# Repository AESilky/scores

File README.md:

# Score Board

Two team score board w/remote for use in the yard when playing different games
like ladder-ball, cornhole, horseshoes, basketball, etc.

Options for two display types:

1. 2 Digits each for Team-A, Team-B, and a third for Period, Time, etc., and 4 indicators for each team.
2. 2 Linear rows of 24 dots each (for Team-A and Team-B), and 4 indicators for each team.

The Digits type is a typical score board that you would use for baseball,
basketball, football, etc. The Linear display is appropriate for games that
go from 0 to some number of points (maximum of 24), like cornhole, ladderball,
horseshoes, etc.

It uses either a remote or switch banks to control the score. It can use the
remote alone, or with a switch bank, or with two switch banks (without the remote).
The switch banks have either 4 or 6 switches. When using two switch banks, there
is a bank for each team that allow increasing/decreasing the score, resetting to
a lower score (typically 11) and to zero.

The board has a Zigby receiver for non line of sight, communication (though not
yet supported).

The board uses multiplexed 7 segment LED displays to provide a two team/player
two digit score, plus a two digit number that can count periods, innings,
quarters, etc., or can count down/up time. There are four LEDs under the score
for each side that can be used to indicate timeouts left, substitutions made,
etc.

The linear display is also multiplexed LEDs, using the segment drives.

The board also has a OLED display panel (SPI) that can also display the score (intended
for the back side to assist a scorekeeper), as well as for use for setup.

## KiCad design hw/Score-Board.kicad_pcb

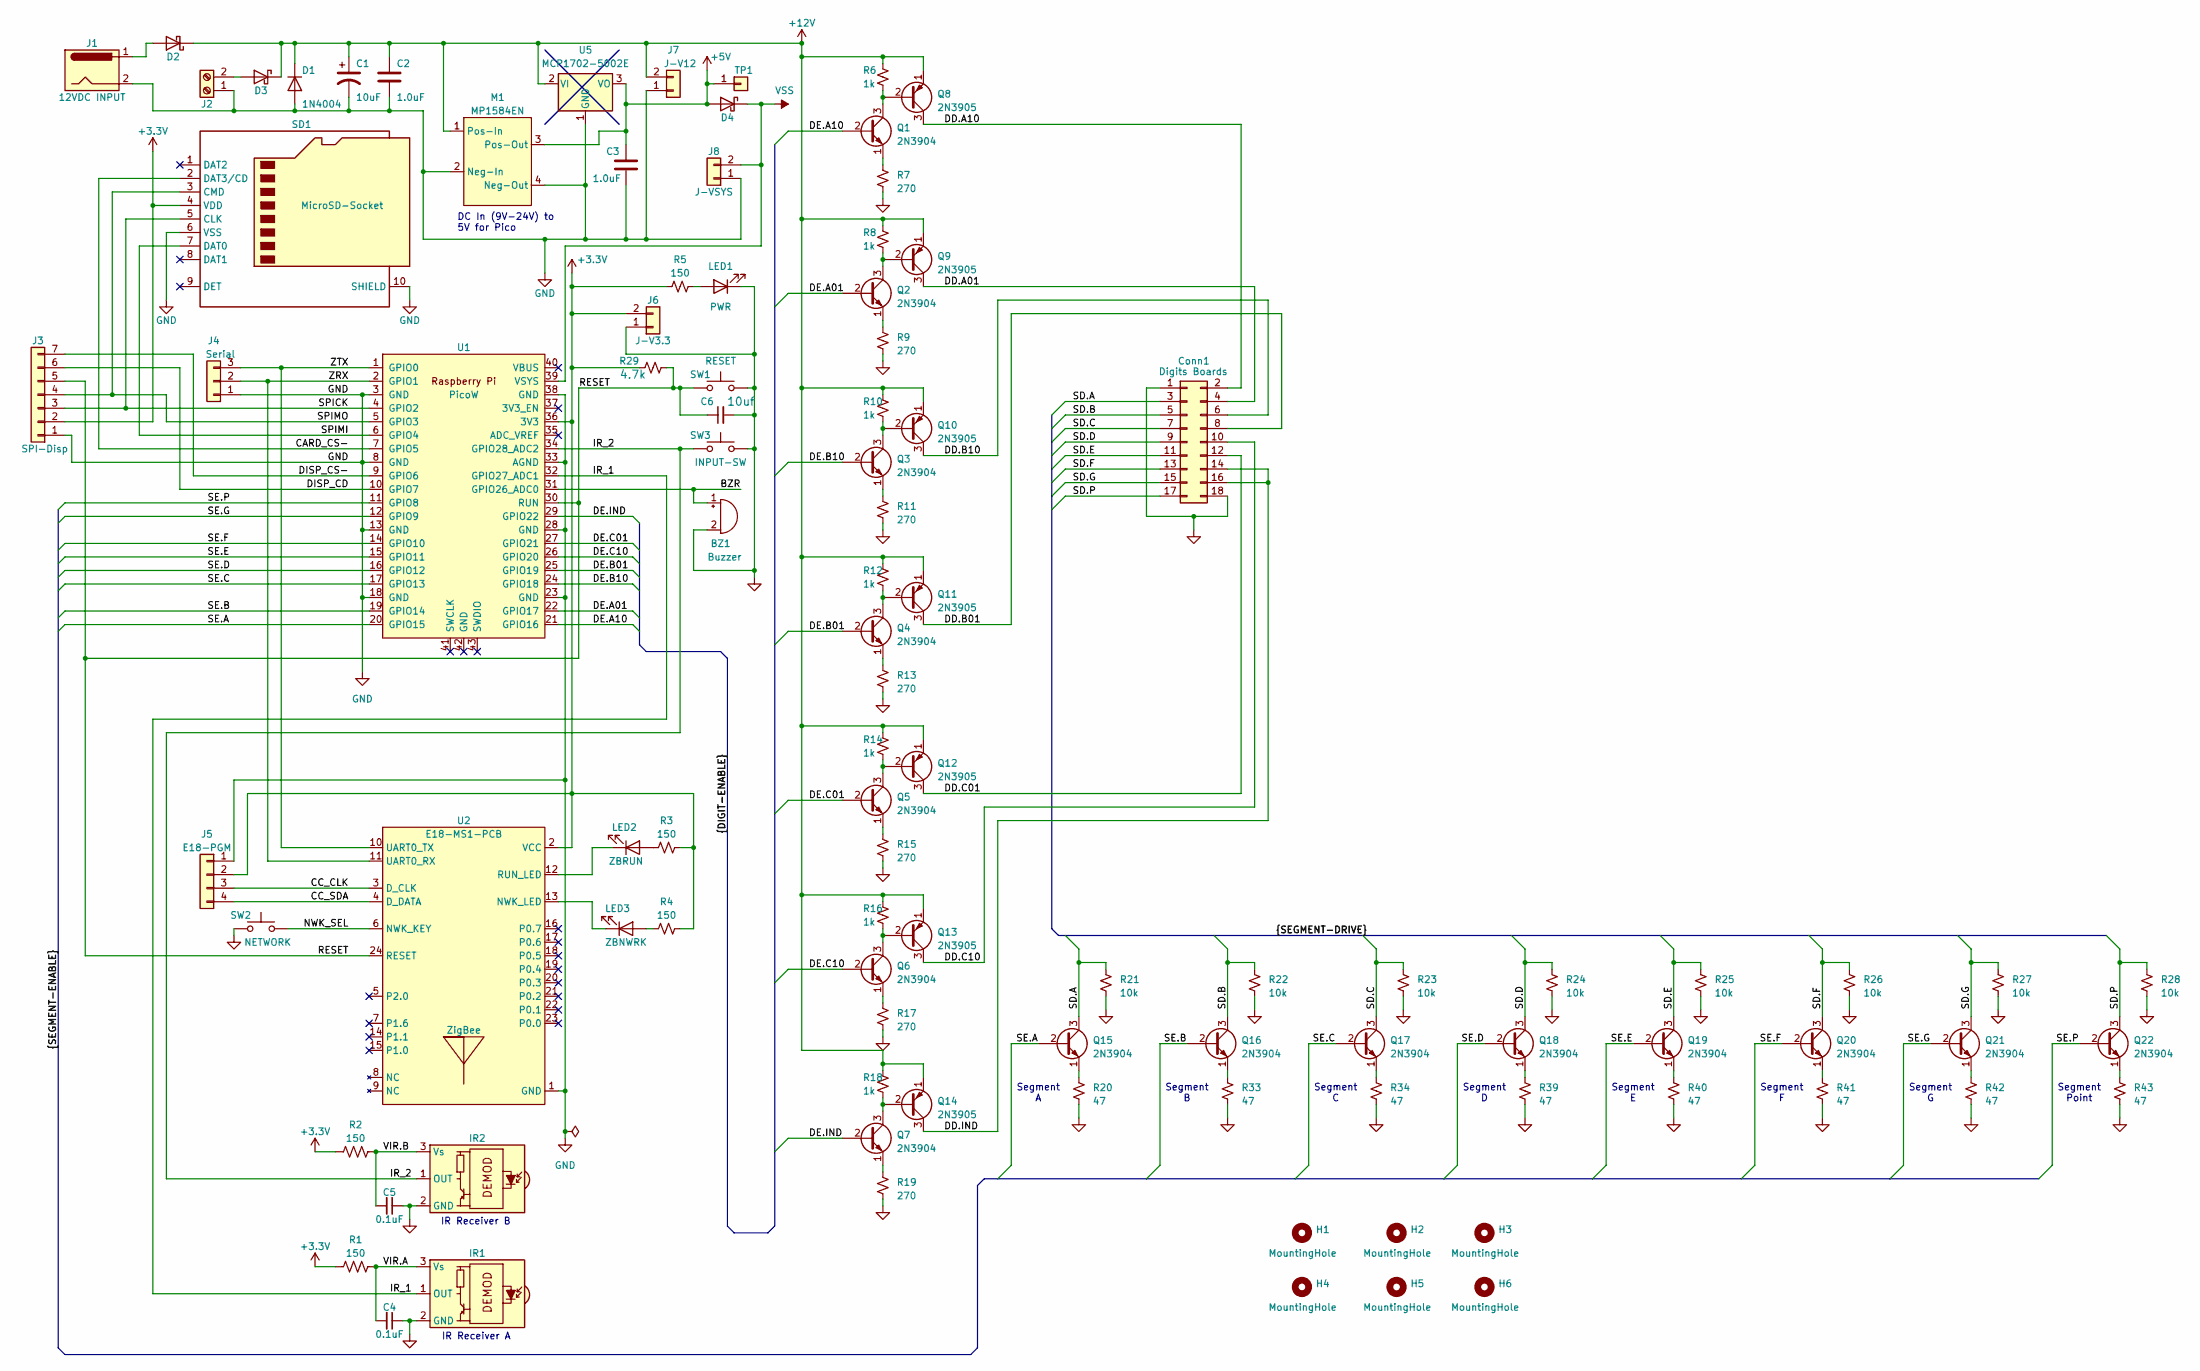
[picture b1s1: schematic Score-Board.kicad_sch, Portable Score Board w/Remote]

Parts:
BZ1: Buzzer; Buzzer_12x9.5RM7.6
C1: 10uF; CP_Radial_D8.0mm_P3.50mm
C2, C3: 1.0uF; CP_Radial_D5.0mm_P2.00mm
C4, C5: 0.1uF; C_Disc_D5.0mm_W2.5mm_P2.50mm
C6: 10uf
Conn1: Conn_02x09_Odd_Even; PinHeader_2x09_P2.54mm_Vertical
D1: 1N4004; D_DO-41_SOD81_P10.16mm_Horizontal
D2, D4: D_Schottky_PP; D_DO-35_SOD27_P10.16mm_Horizontal
D3: D_Schottky; D_DO-35_SOD27_P10.16mm_Horizontal
H1, H2, H3, H4, H5, H6: MountingHole; MountingHole_3.2mm_M3
IR1, IR2: TSOP382xx; Vishay_MINICAST-3Pin
J1: Barrel_Jack; CUI_PJ-037B
J2: Screw_Terminal_01x02; TerminalBlock_Philmore_TB132_1x02_P5.00mm_Horizontal
J3: SPI-Disp; PinSocket_1x07_P2.54mm_Vertical
J4: Conn_01x03; PinHeader_1x03_P2.54mm_Vertical
J5: Conn_01x04; PinHeader_1x04_P2.54mm_Vertical
J6: J-V3.3; PinHeader_1x02_P2.54mm_Vertical
J7: J-V12; PinHeader_1x02_P2.54mm_Vertical
J8: J-VSYS; PinHeader_1x02_P2.54mm_Vertical
LED1: PWR; LED_D5.0mm
LED2: ZBRUN; LED_D5.0mm
LED3: ZBNWRK; LED_D5.0mm
M1: MP1584EN
Q1, Q2, Q3, Q4, Q5, Q6, Q7, Q15, Q16, Q17, Q18, Q19, Q20, Q21, Q22: 2N3904; TO-92_Inline
Q8, Q9, Q10, Q11, Q12, Q13, Q14: 2N3905; TO-92_Inline
R1, R2, R3, R4, R5: 150; R_Axial_DIN0207_L6.3mm_D2.5mm_P10.16mm_Horizontal
R6, R8, R10, R12, R14, R16, R18: 1k; R_Axial_DIN0207_L6.3mm_D2.5mm_P10.16mm_Horizontal
R7, R9, R11, R13, R15, R17, R19: 270; R_Axial_DIN0207_L6.3mm_D2.5mm_P10.16mm_Horizontal
R20, R33, R34, R39, R40, R41, R42, R43: 47; R_Axial_DIN0207_L6.3mm_D2.5mm_P10.16mm_Horizontal
R21, R22, R23, R24, R25, R26, R27, R28: 10k; R_Axial_DIN0207_L6.3mm_D2.5mm_P10.16mm_Horizontal
R29: 4.7k; R_Axial_DIN0207_L6.3mm_D2.5mm_P10.16mm_Horizontal
SD1: MicroSD-Socket; SDCard-GCT_MEM2075-00-140-01-A
SW1: RESET; SW_TL1100F160Q
SW2: NETWORK; SW_TL1100F160Q
SW3: INPUT-SW; SW_TL1100F160Q
TP1: Conn_01x01; PinHeader_1x01_P2.54mm_Vertical
U1: PicoW; RPi_PicoW_SMD_TH
U2: E18-MS1-PCB; E18-MS1-PCB-AES
U5: MCP1702-5002E; TO-92_Inline

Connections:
+3.3V: J3.2, J5.2, J6.2, R1.1 (I), R2.1 (I), R3.2, R4.2, R5.1, R29.1, SD1.4 (VDD), U1.36 (3V3), U2.2 (VCC)
+5V: C3.1, D4.2 (A), M1.3 (Pos-Out), TP1.1, U5.3 (VO)
+12V: C1.1, C2.1, D1.1 (K), D2.1 (K), D3.1 (K), J7.2, M1.1 (Pos-In), Q8.1 (E), Q9.1 (E), Q10.1 (E), Q11.1 (E), Q12.1 (E), Q13.1 (E), Q14.1 (E), R6.1, R8.1, R10.1, R12.1, R14.1, R16.1, R18.1, U5.2 (VI)
/BZR: BZ1.1 (-), U1.31 (GPIO26_ADC0)
/CARD_CS-: SD1.2 (DAT3/CD), U1.7 (GPIO5)
/CC_CLK: J5.3, U2.3 (D_CLK)
/CC_SDA: J5.4, U2.4 (D_DATA)
/DD.A01: Conn1.4, Q9.3 (C)
/DD.A10: Conn1.2, Q8.3 (C)
/DD.B01: Conn1.8, Q11.3 (C)
/DD.B10: Conn1.6, Q10.3 (C)
/DD.C01: Conn1.12, Q12.3 (C)
/DD.C10: Conn1.10, Q13.3 (C)
/DD.IND: Conn1.14, Conn1.16, Q14.3 (C)
/DE.A01: Q2.2 (B), U1.22 (GPIO17)
/DE.A10: Q1.2 (B), U1.21 (GPIO16)
/DE.B01: Q4.2 (B), U1.25 (GPIO19)
/DE.B10: Q3.2 (B), U1.24 (GPIO18)
/DE.C01: Q5.2 (B), U1.27 (GPIO21)
/DE.C10: Q6.2 (B), U1.26 (GPIO20)
/DE.IND: Q7.2 (B), U1.29 (GPIO22)
/DISP_CD: J3.6, U1.10 (GPIO7)
/DISP_CS-: J3.7, U1.9 (GPIO6)
/IR_1: IR1.1 (OUT), U1.32 (GPIO27_ADC1)
/IR_2: IR2.1 (OUT), SW3.1, U1.34 (GPIO28_ADC2)
/NWK_SEL: SW2.2, U2.6 (NWK_KEY)
/RESET: C6.1, J3.5, R29.2, SW1.1, U1.30 (RUN), U2.24 (RESET)
/SD.A: Conn1.3, Q15.3 (C), R21.1
/SD.B: Conn1.5, Q16.3 (C), R22.1
/SD.C: Conn1.7, Q17.3 (C), R23.1
/SD.D: Conn1.9, Q18.3 (C), R24.1
/SD.E: Conn1.11, Q19.3 (C), R25.1
/SD.F: Conn1.13, Q20.3 (C), R26.1
/SD.G: Conn1.15, Q21.3 (C), R27.1
/SD.P: Conn1.17, Q22.3 (C), R28.1
/SE.A: Q15.2 (B), U1.20 (GPIO15)
/SE.B: Q16.2 (B), U1.19 (GPIO14)
/SE.C: Q17.2 (B), U1.17 (GPIO13)
/SE.D: Q18.2 (B), U1.16 (GPIO12)
/SE.E: Q19.2 (B), U1.15 (GPIO11)
/SE.F: Q20.2 (B), U1.14 (GPIO10)
/SE.G: Q21.2 (B), U1.12 (GPIO9)
/SE.P: Q22.2 (B), U1.11 (GPIO8)
/SPICK: J3.3, SD1.5 (CLK), U1.4 (GPIO2)
/SPIMI: SD1.7 (DAT0), U1.6 (GPIO4)
/SPIMO: J3.4, SD1.3 (CMD), U1.5 (GPIO3)
/VIR.A: C4.2, IR1.3 (Vs), R1.2 (O)
/VIR.B: C5.2, IR2.3 (Vs), R2.2 (O)
/ZRX: J4.2, U1.2 (GPIO1), U2.11 (UART0_RX)
/ZTX: J4.3, U1.1 (GPIO0), U2.10 (UART0_TX)
GND: BZ1.2 (+), C1.2, C2.2, C3.2, C4.1, C5.1, C6.2, Conn1.1, Conn1.18, D1.2 (A), IR1.2 (GND), IR2.2 (GND), J1.2, J2.1, J3.1, J4.1, J5.1, J6.1, J7.1, J8.1, LED1.1 (K), M1.2 (Neg-In), M1.4 (Neg-Out), R7.2, R9.2, R11.2, R13.2, R15.2, R17.2, R19.2, R20.2, R21.2, R22.2, R23.2, R24.2, R25.2, R26.2, R27.2, R28.2, R33.2, R34.2, R39.2, R40.2, R41.2, R42.2, R43.2, SD1.6 (VSS), SD1.10 (SHIELD), SW1.2, SW2.1, SW3.2, U1.3 (GND), U1.8 (GND), U1.13 (GND), U1.18 (GND), U1.23 (GND), U1.28 (GND), U1.33 (AGND), U1.38 (GND), U2.1 (GND), U5.1 (GND)
unnamed: D2.2 (A), J1.1
unnamed: D3.2 (A), J2.2
unnamed: LED1.2 (A), R5.2
unnamed: LED2.2 (A), R3.1
unnamed: LED2.1 (K), U2.12 (RUN_LED)
unnamed: LED3.2 (A), R4.1
unnamed: LED3.1 (K), U2.13 (NWK_LED)
unnamed: Q1.3 (C), Q8.2 (B), R6.2
unnamed: Q1.1 (E), R7.1
unnamed: Q2.3 (C), Q9.2 (B), R8.2
unnamed: Q2.1 (E), R9.1
unnamed: Q3.1 (E), R11.1
unnamed: Q4.1 (E), R13.1
unnamed: Q5.1 (E), R15.1
unnamed: Q6.1 (E), R17.1
unnamed: Q7.1 (E), R19.1
unnamed: Q3.3 (C), Q10.2 (B), R10.2
unnamed: Q4.3 (C), Q11.2 (B), R12.2
unnamed: Q5.3 (C), Q12.2 (B), R14.2
unnamed: Q6.3 (C), Q13.2 (B), R16.2
unnamed: Q7.3 (C), Q14.2 (B), R18.2
unnamed: Q15.1 (E), R20.1
unnamed: Q16.1 (E), R33.1
unnamed: Q17.1 (E), R34.1
unnamed: Q18.1 (E), R39.1
unnamed: Q19.1 (E), R40.1
unnamed: Q20.1 (E), R41.1
unnamed: Q21.1 (E), R42.1
unnamed: Q22.1 (E), R43.1
VSS: D4.1 (K), J8.2, U1.39 (VSYS)

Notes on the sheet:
Segment E
Segment C
Segment B
Segment D
Segment G
Segment A
Segment F
Segment Point
IR Receiver B
DC In (9V-24V) to 5V for Pico
IR Receiver A

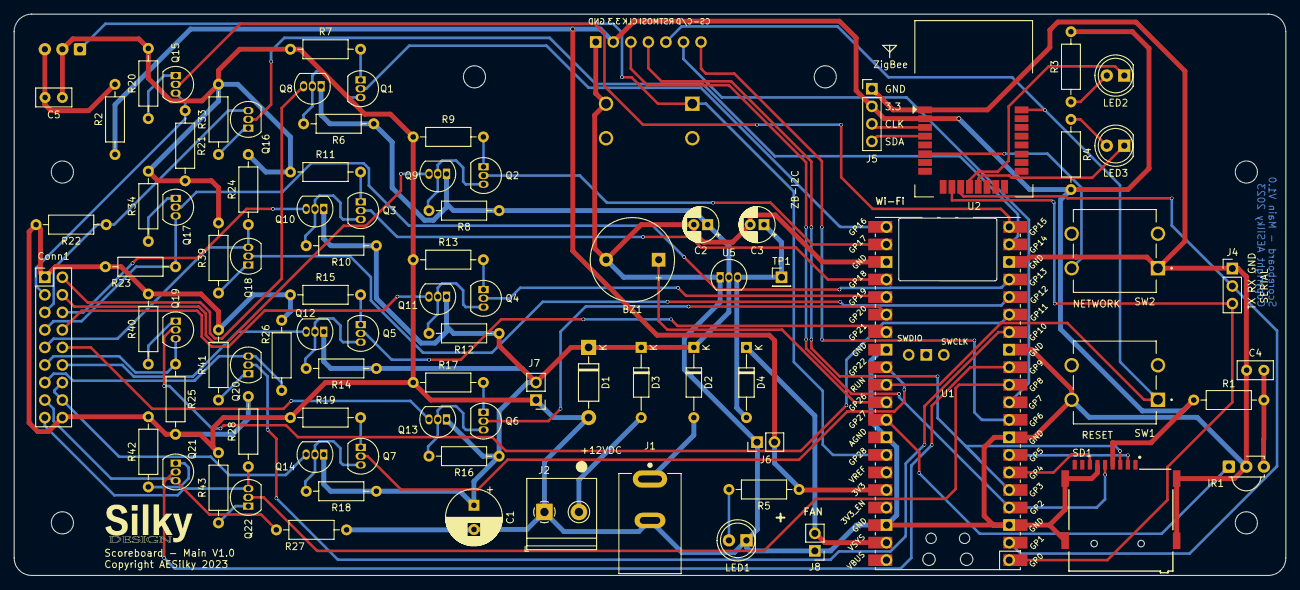
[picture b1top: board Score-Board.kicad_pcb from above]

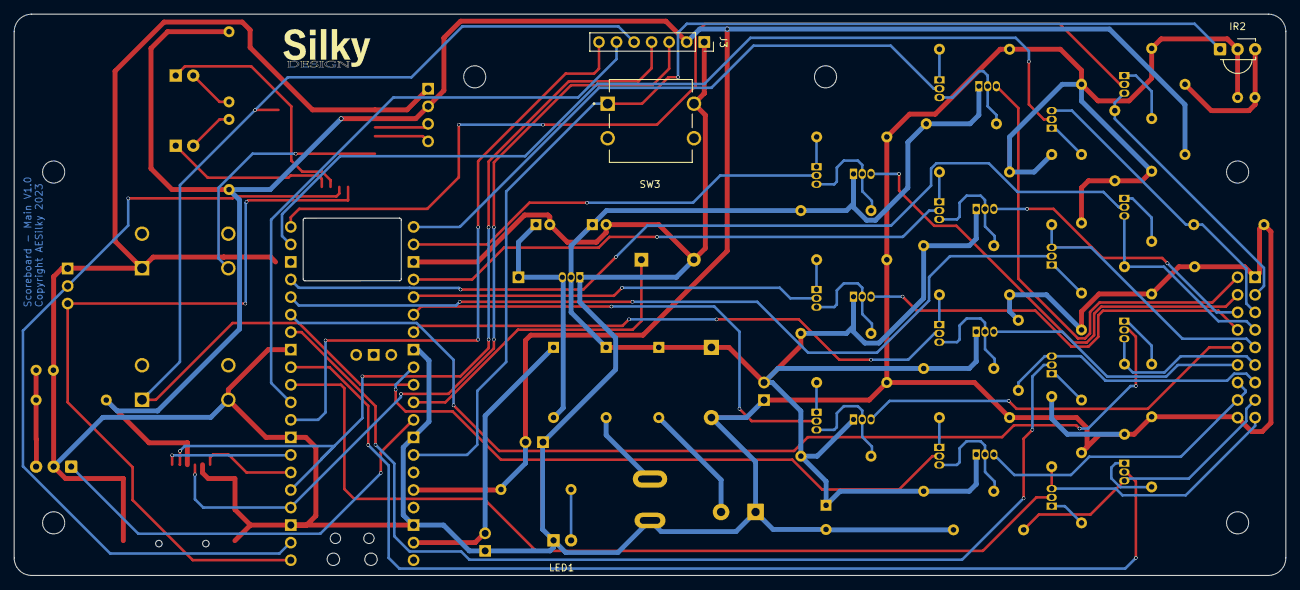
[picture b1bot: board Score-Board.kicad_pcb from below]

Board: 2 copper layers, 184.2 x 81.3 mm, 95 parts (3 on the bottom side), 81 nets.

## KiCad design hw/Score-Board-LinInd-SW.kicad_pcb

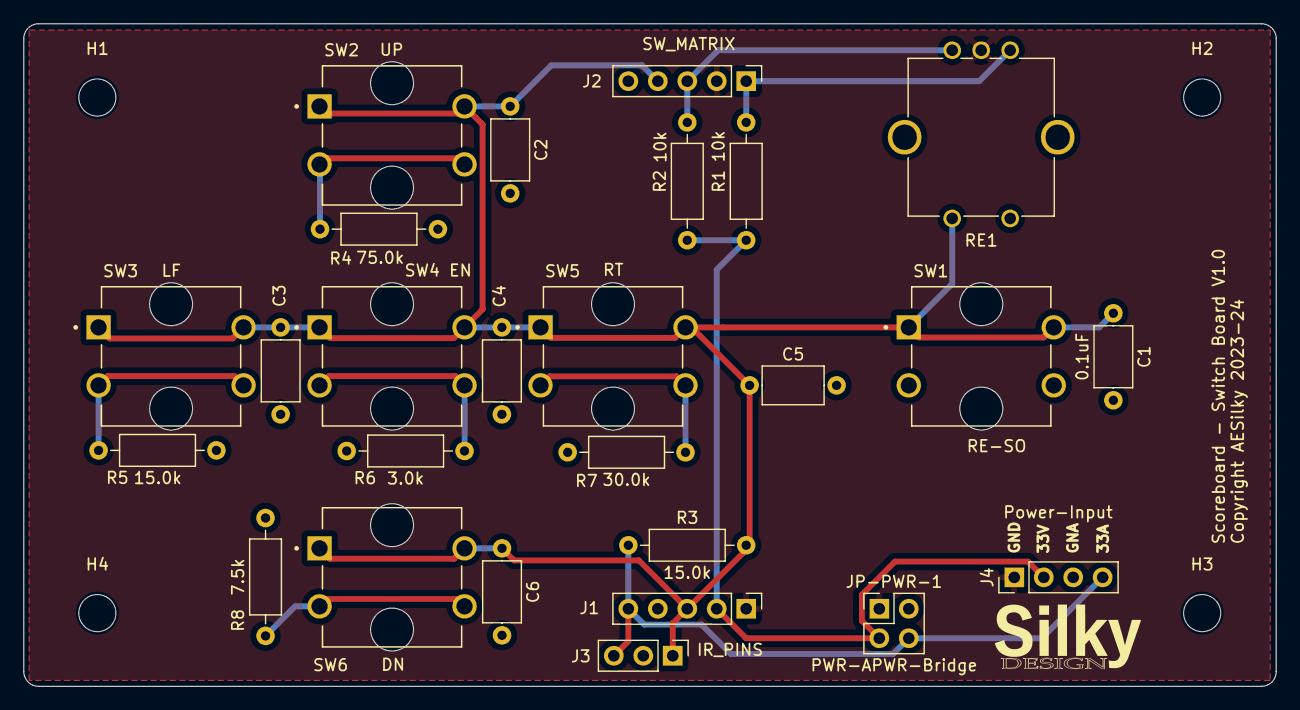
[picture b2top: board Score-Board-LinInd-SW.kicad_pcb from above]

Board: 2 copper layers, 108.0 x 57.1 mm, 31 parts (0 on the bottom side), 12 nets.

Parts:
C1, C2, C3, C4, C5, C6: 0.1uF; C_Axial_L5.1mm_D3.1mm_P7.50mm_Horizontal
G1: LOGO; SILKY-DESIGN-logo-0_50-AES
H1, H2, H3, H4: MountingHole; MountingHole_3.2mm_M3
J1: IR_PINS; PinHeader_1x05_P2.54mm_Vertical
J2: SW_MATRIX; PinHeader_1x05_P2.54mm_Vertical
J3: IR_CONN; PinHeader_1x03_P2.54mm_Vertical
J4: Power-Input; PinHeader_1x04_P2.54mm_Vertical
JP-PWR-1: PWR-APWR-Bridge; PinHeader_2x02_P2.54mm_Vertical
R1, R2: 10k; R_Axial_DIN0207_L6.3mm_D2.5mm_P10.16mm_Horizontal
R3, R5: 15.0k; R_Axial_DIN0207_L6.3mm_D2.5mm_P10.16mm_Horizontal
R4: 75.0k; R_Axial_DIN0207_L6.3mm_D2.5mm_P10.16mm_Horizontal
R6: 3.0k; R_Axial_DIN0207_L6.3mm_D2.5mm_P10.16mm_Horizontal
R7: 30.0k; R_Axial_DIN0207_L6.3mm_D2.5mm_P10.16mm_Horizontal
R8: 7.5k; R_Axial_DIN0207_L6.3mm_D2.5mm_P10.16mm_Horizontal
RE1: RotEnc-SW; RotaryEncoder_Bourns_Vertical_PEC12R-3xxxF-Sxxxx
SW1: RE-SO; AES-SW_PUSH_TH_1P1T_12mm
SW2: UP; AES-SW_PUSH_TH_1P1T_12mm
SW3: LF; AES-SW_PUSH_TH_1P1T_12mm
SW4: EN; AES-SW_PUSH_TH_1P1T_12mm
SW5: RT; AES-SW_PUSH_TH_1P1T_12mm
SW6: DN; AES-SW_PUSH_TH_1P1T_12mm

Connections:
+3.3V: J1.2, J4.2, JP-PWR-1.3, R1.1, R2.1
+3.3VA: J1.5, J3.3, J4.4, JP-PWR-1.4, R3.1
/RE_A: J2.1, R1.2, RE1.A
/RE_B: J2.3, R2.2, RE1.B
/SW_MTRX: C1.1, C2.1, C3.1, C4.1, C5.1, C6.1, J1.3, J2.4, J3.1, R3.2, RE1.S2, SW1.1, SW1.2, SW2.1, SW2.2, SW3.1, SW3.2, SW4.1, SW4.2, SW5.1, SW5.2, SW6.1, SW6.2
GND: J1.1, J2.2, J4.1, JP-PWR-1.1, RE1.C
GNDA: C1.2, C2.2, C3.2, C4.2, C5.2, C6.2, J1.4, J2.5, J3.2, J4.3, JP-PWR-1.2, R4.1, R5.1, R6.1, R7.1, R8.1, RE1.S1, SW1.3, SW1.4
unnamed: R4.2, SW2.3, SW2.4
unnamed: R5.2, SW3.3, SW3.4
unnamed: R6.2, SW4.3, SW4.4
unnamed: R7.2, SW5.3, SW5.4
unnamed: R8.2, SW6.3, SW6.4

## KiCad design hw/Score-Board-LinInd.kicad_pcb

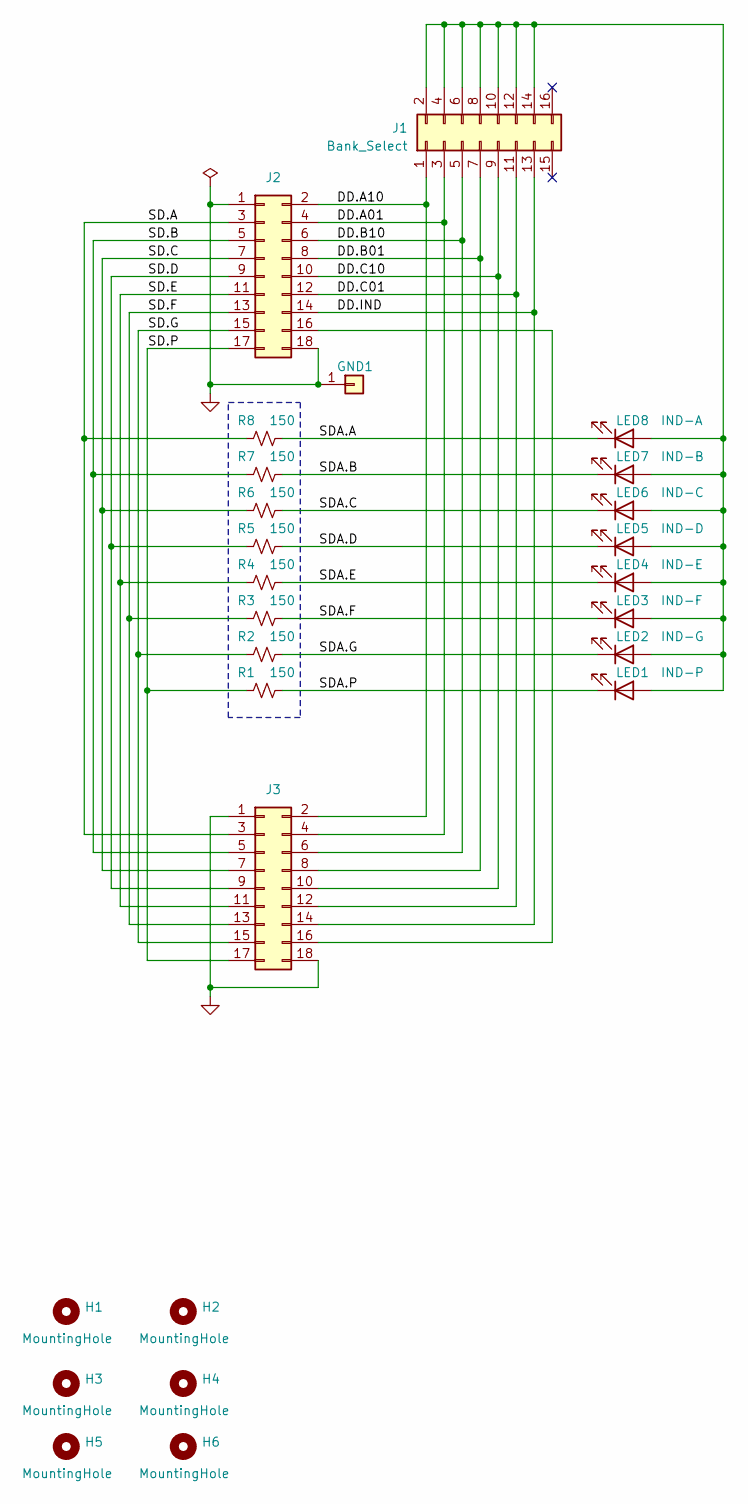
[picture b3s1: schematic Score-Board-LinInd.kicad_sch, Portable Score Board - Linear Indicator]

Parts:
GND1: Conn_01x01; PinHeader_1x01_P2.54mm_Vertical
H1, H2, H3, H4, H5, H6: MountingHole; MountingHole_3.2mm_M3
J1: Bank_Select; PinHeader_2x08_P2.54mm_Vertical
J2, J3: DigSeg-Drive; PinHeader_2x09_P2.54mm_Vertical
LED1: IND-P; LED_D10.0mm
LED2: IND-G; LED_D10.0mm
LED3: IND-F; LED_D10.0mm
LED4: IND-E; LED_D10.0mm
LED5: IND-D; LED_D10.0mm
LED6: IND-C; LED_D10.0mm
LED7: IND-B; LED_D10.0mm
LED8: IND-A; LED_D10.0mm
R1, R2, R3, R4, R5, R6, R7, R8: 150; R_Axial_DIN0207_L6.3mm_D2.5mm_P10.16mm_Horizontal

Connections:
/DD.A01: J1.3, J2.4, J3.4
/DD.A10: J1.1, J2.2, J3.2
/DD.B01: J1.7, J2.8, J3.8
/DD.B10: J1.5, J2.6, J3.6
/DD.C01: J1.11, J2.12, J3.12
/DD.C10: J1.9, J2.10, J3.10
/DD.IND: J1.13, J2.14, J3.14
/SD.A: J2.3, J3.3, R8.1
/SD.B: J2.5, J3.5, R7.1
/SD.C: J2.7, J3.7, R6.1
/SD.D: J2.9, J3.9, R5.1
/SD.E: J2.11, J3.11, R4.1
/SD.F: J2.13, J3.13, R3.1
/SD.G: J2.15, J3.15, R2.1
/SD.P: J2.17, J3.17, R1.1
/SDA.A: LED8.1 (K), R8.2
/SDA.B: LED7.1 (K), R7.2
/SDA.C: LED6.1 (K), R6.2
/SDA.D: LED5.1 (K), R5.2
/SDA.E: LED4.1 (K), R4.2
/SDA.F: LED3.1 (K), R3.2
/SDA.G: LED2.1 (K), R2.2
/SDA.P: LED1.1 (K), R1.2
GND: GND1.1, J2.1, J2.18, J3.1, J3.18
unnamed: J1.2, J1.4, J1.6, J1.8, J1.10, J1.12, J1.14, LED1.2 (A), LED2.2 (A), LED3.2 (A), LED4.2 (A), LED5.2 (A), LED6.2 (A), LED7.2 (A), LED8.2 (A)
unnamed: J2.16, J3.16

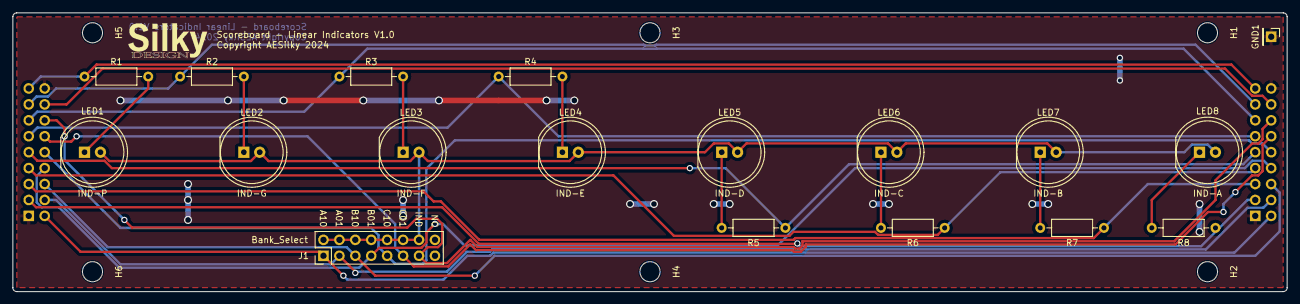
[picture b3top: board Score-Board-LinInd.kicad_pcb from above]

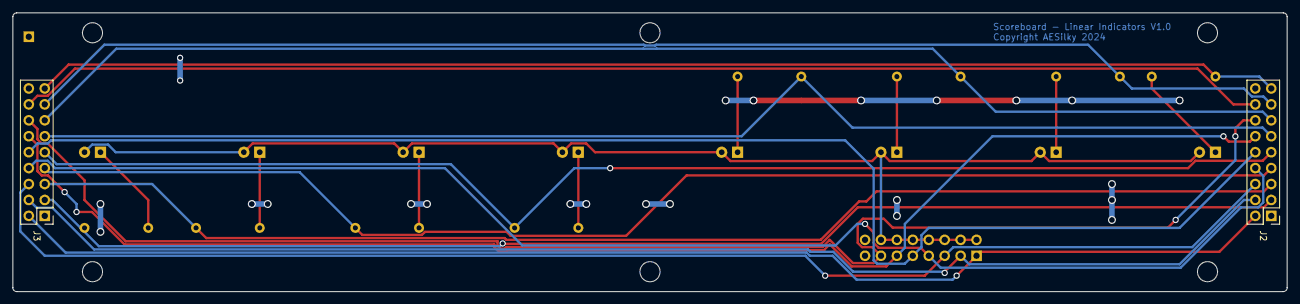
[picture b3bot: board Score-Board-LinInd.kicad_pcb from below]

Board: 2 copper layers, 203.2 x 44.5 mm, 27 parts (2 on the bottom side), 26 nets.

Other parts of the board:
G1: LOGO; SILKY-DESIGN-logo-0_50-AES

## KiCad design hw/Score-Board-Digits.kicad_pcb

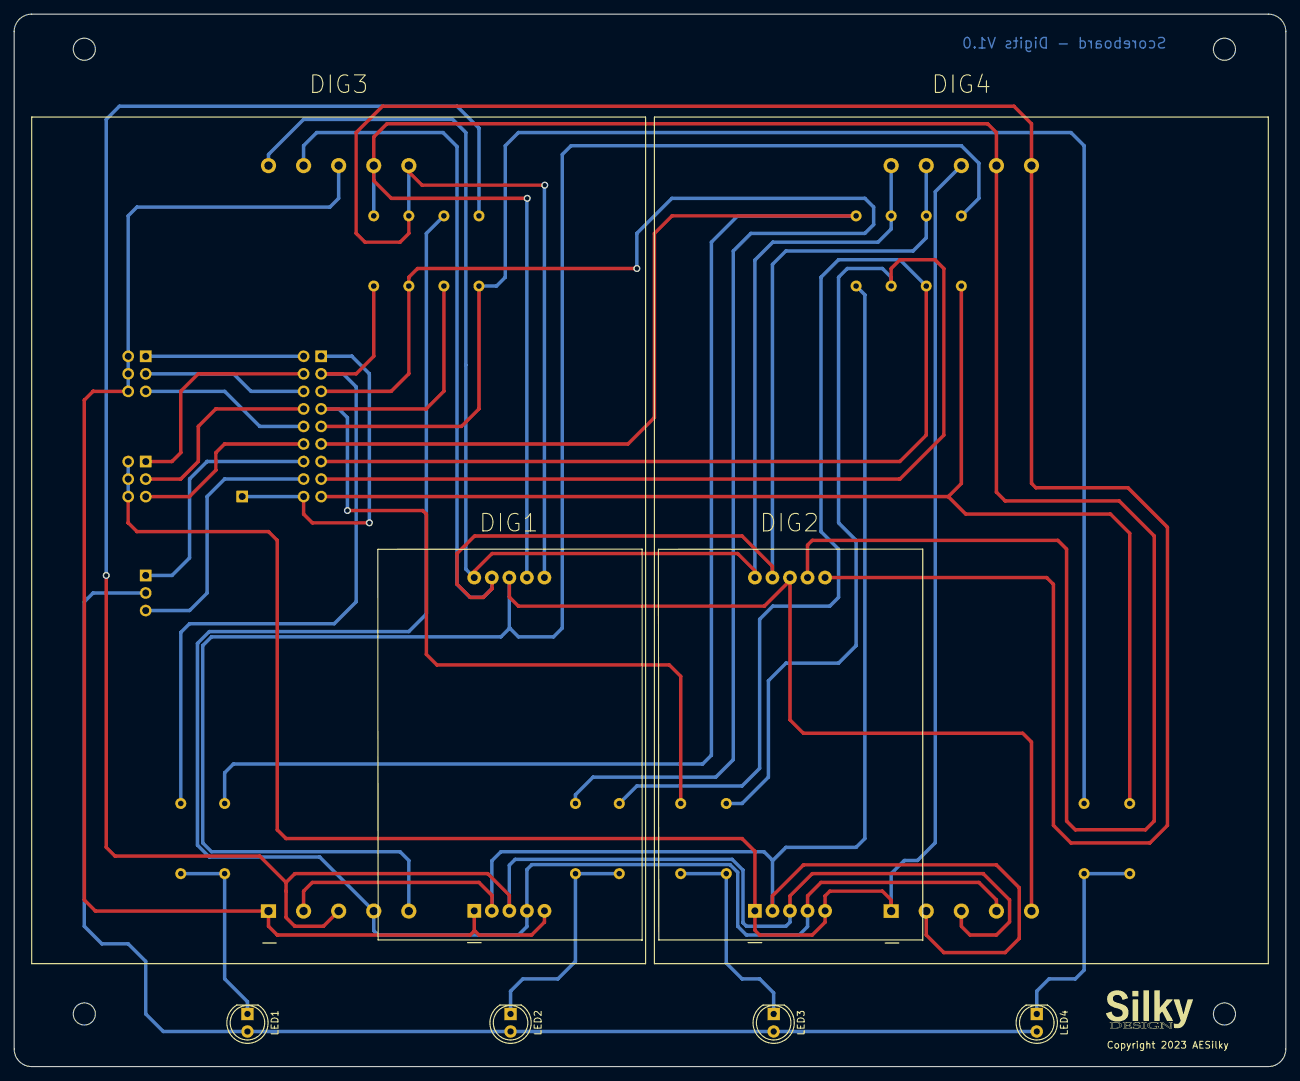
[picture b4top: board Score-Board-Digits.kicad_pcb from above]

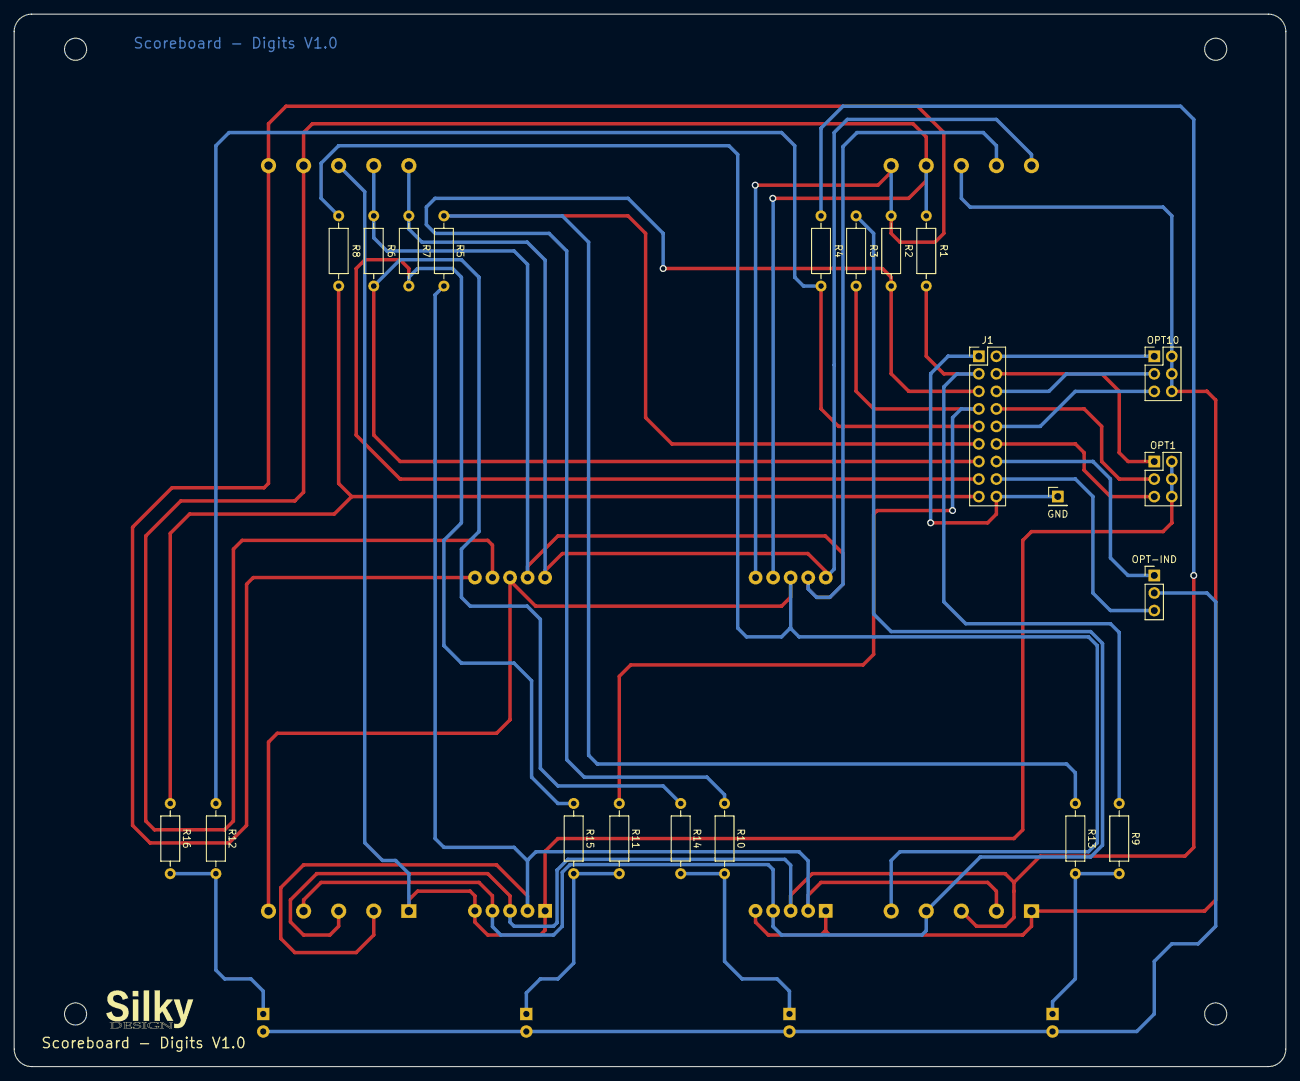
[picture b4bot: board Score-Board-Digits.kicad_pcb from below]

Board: 2 copper layers, 184.1 x 152.4 mm, 33 parts (21 on the bottom side), 32 nets.

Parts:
DIG1, DIG2: WJLEDS18012TUR11; DISP-CL18011BS-AES
DIG3, DIG4: WJLEDS40012TUR11; DISP-40101BCR-AES
GND: Conn_01x01; PinHeader_1x01_P2.54mm_Vertical
H1, H2, H3, H4: MountingHole; MountingHole_3.2mm_M3
J1: Conn_02x09_Odd_Even; PinHeader_2x09_P2.54mm_Vertical
LED1: IND-A1; LED_D5.0mm
LED2: IND-A2; LED_D5.0mm
LED3: IND-A3; LED_D5.0mm
LED4: IND-A4; LED_D5.0mm
OPT1, OPT10: Conn_02x03_Odd_Even; PinHeader_2x03_P2.54mm_Vertical
OPT-IND: Opt_1-2; PinHeader_1x03_P2.54mm_Vertical
R1, R2, R3, R4, R5, R6, R7: 77; R_Axial_DIN0207_L6.3mm_D2.5mm_P10.16mm_Horizontal
R8, R9, R10, R11, R12, R13, R14, R15, R16: 100; R_Axial_DIN0207_L6.3mm_D2.5mm_P10.16mm_Horizontal

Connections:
/SD.A: J1.3, R1.1, R9.1
/SD.B: J1.5, R2.1, R10.1
/SD.C: J1.7, R3.1, R11.1
/SD.D: J1.9, R4.1, R12.1
/SD.E: J1.11, R5.1, R13.1
/SD.F: J1.13, R6.1, R14.1
/SD.G: J1.15, R7.1, R15.1
/SD.P: J1.17, R8.1, R16.1
/SDA.A: DIG1.7 (A), DIG2.7 (A), DIG3.7 (A), DIG4.7 (A), R1.2
/SDA.B: DIG1.6 (B), DIG2.6 (B), DIG3.6 (B), DIG4.6 (B), R2.2
/SDA.C: DIG1.4 (C), DIG2.4 (C), DIG3.4 (C), DIG4.4 (C), R3.2
/SDA.D: DIG1.3 (D), DIG2.3 (D), DIG3.3 (D), DIG4.3 (D), R4.2
/SDA.E: DIG1.2 (E), DIG2.2 (E), DIG3.2 (E), DIG4.2 (E), R5.2
/SDA.F: DIG1.9 (F), DIG2.9 (F), DIG3.9 (F), DIG4.9 (F), R6.2
/SDA.G: DIG1.10 (G), DIG2.10 (G), DIG3.10 (G), DIG4.10 (G), R7.2
/SDA.P: DIG1.8 (DP), DIG2.8 (DP), DIG3.5 (DP), DIG4.5 (DP), R8.2
GND: GND.1, J1.1, J1.18
unnamed: J1.2, OPT10.1
unnamed: J1.4, OPT1.1
unnamed: J1.6, OPT10.3
unnamed: J1.8, OPT1.3
unnamed: J1.10, OPT10.5
unnamed: J1.12, OPT1.5
unnamed: J1.14, OPT-IND.1 (Pin_A)
unnamed: J1.16, OPT-IND.3 (Pin_B)
unnamed: LED1.2 (A), LED2.2 (A), LED3.2 (A), LED4.2 (A), OPT-IND.2 (Pin_Common)
unnamed: LED1.1 (K), R9.2, R13.2
unnamed: LED2.1 (K), R10.2, R14.2
unnamed: LED3.1 (K), R11.2, R15.2
unnamed: LED4.1 (K), R12.2, R16.2
unnamed: DIG2.1 (CA), DIG2.5 (CA), DIG4.1 (CA), DIG4.8 (CA), OPT1.2, OPT1.4, OPT1.6
unnamed: DIG1.1 (CA), DIG1.5 (CA), DIG3.1 (CA), DIG3.8 (CA), OPT10.2, OPT10.4, OPT10.6

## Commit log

2023-06-14 Full schematic. ERC not passing yet.
2023-06-17 Schematic complete v0.1. Ready for layout.
2023-06-18 Schematic updated with 3 digit boards
2023-06-18 Schematic updated with digit drive resistors
2023-06-19 Footprints assigned
2023-06-19 Separate Main and Digits projects
2023-06-20 Digits schmatic ready for layout
2023-06-20 Initial PCB component placement
2023-06-21 PCB routed v1
2023-06-21 Main schematic ready for board layout
2023-07-01 PCB routing done
2023-07-03 Initial source code
2023-07-14 Code ready to test basic functionality.
2023-07-15 Reorganized includes and separate config_cmd out of config.
2023-07-15 SW running. Initial debug.
2023-07-18 Add pull-down res to segment drives.
2023-07-22 SPI for display & SD, Seg&Dig enables 16 straight GPIOs.
2023-07-22 Add board cutout for Wi-Fi ant area of Pico-W.
2023-08-06 v1.0 Board
2024-07-22 Linear Style: Panel and Switches boards.
2024-07-23 Scorekeeper with Numeric and Linear panels. (plus repair)
2024-07-23 Workspace: Fix workspace and build on Linux.
2024-07-23 Workspace: Move VSCode WS to root.
2024-08-15 IR Remote working.
2024-08-15 README update
2024-08-24 BOM generated.
2024-08-28 Info updates
2024-09-16 Add 3rd party license info.
2024-09-16 Fix typo in LICENSE-3rdParty.md

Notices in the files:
hw/Score-Board-Digits.kicad_pcb:
Copyright AESilky 2023
Copyright 2023 AESilky
hw/Score-Board-LinInd-SW.kicad_pcb:
Copyright 2023-24 AESilky
Copyright AESilky 2023-24
hw/Score-Board-LinInd.kicad_pcb:
Copyright AESilky 2024
